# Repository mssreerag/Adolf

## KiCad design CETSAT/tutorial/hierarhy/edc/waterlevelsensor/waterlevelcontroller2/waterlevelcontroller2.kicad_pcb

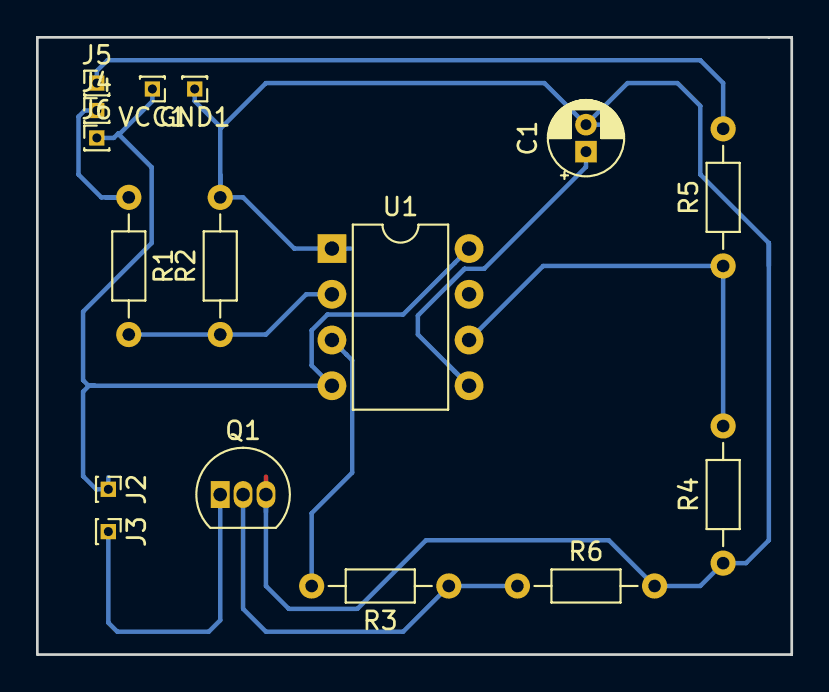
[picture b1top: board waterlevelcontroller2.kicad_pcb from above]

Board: 2 copper layers, 41.9 x 34.3 mm, 16 parts (0 on the bottom side), 10 nets.

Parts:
C1: 0.01u; CP_Radial_D4.0mm_P1.50mm
GND1: Conn_01x01_Male; PinHeader_1x01_P1.00mm_Vertical
J2, J3, J4, J5, J6: Conn_01x01_Male; PinHeader_1x01_P1.00mm_Vertical
Q1: BC547; TO-92_Inline
R1, R3, R5: 10k; R_Axial_DIN0204_L3.6mm_D1.6mm_P7.62mm_Horizontal
R2, R4: 1M; R_Axial_DIN0204_L3.6mm_D1.6mm_P7.62mm_Horizontal
R6: 100k; R_Axial_DIN0204_L3.6mm_D1.6mm_P7.62mm_Horizontal
U1: LM555; DIP-8_W7.62mm
VCC1: Conn_01x01_Male; PinHeader_1x01_P1.00mm_Vertical

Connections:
4: J2.1, J6.1, U1.4, U1.8, VCC1.1
Earth: C1.2, GND1.1, Q1.3, R2.2, R4.1, R6.2, U1.1
unnamed: C1.1, U1.5
unnamed: J3.1, Q1.1
unnamed: J4.1, R1.1
unnamed: J5.1, R5.2
unnamed: Q1.2, R3.1, R6.1
unnamed: R1.2, R2.1, U1.2
unnamed: R3.2, U1.3
unnamed: R4.2, R5.1, U1.6

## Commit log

2019-02-23 first
2019-02-23 next
2019-02-23 full
